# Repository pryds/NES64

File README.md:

# Moved

The NES64 project has moved to [GitLab](https://gitlab.com/nes64/NES64)

NES64 homepage: [nes64.autumnhippo.com](http://nes64.autumnhippo.com)

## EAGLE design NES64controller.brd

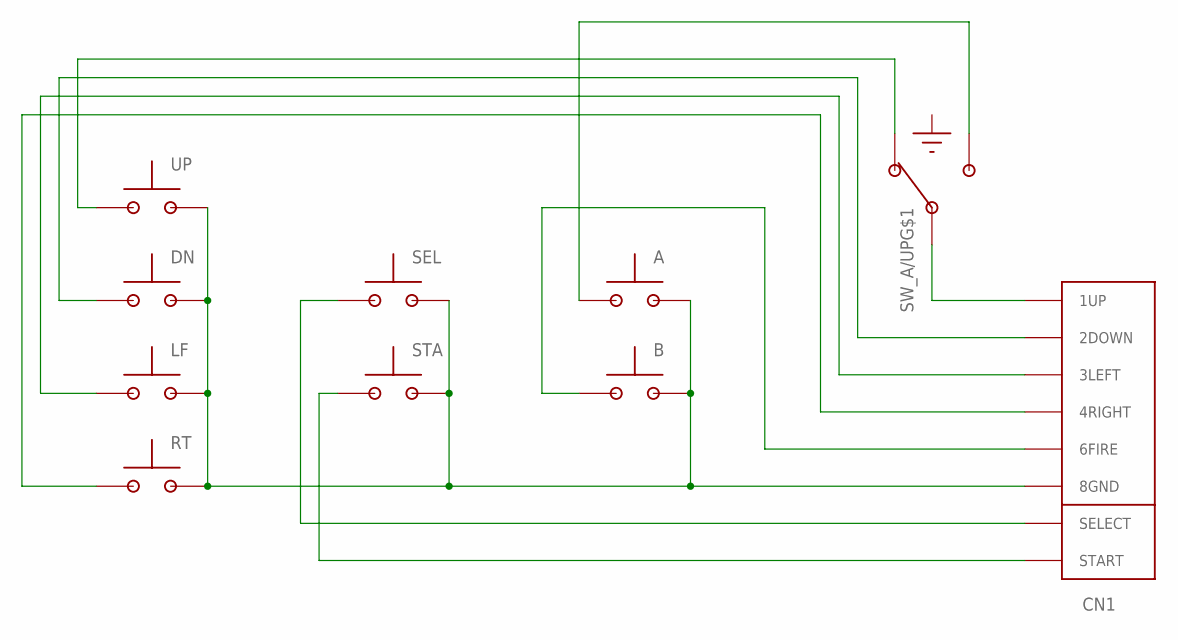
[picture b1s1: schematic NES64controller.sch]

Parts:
A: RUBBERBUTTON_CONTACTAREA_9MM
B: RUBBERBUTTON_CONTACTAREA_9MM
CN1: NES64_CONNECTOR
DN: RUBBERBUTTON_CONTACTAREA_9MM
LF: RUBBERBUTTON_CONTACTAREA_9MM
RT: RUBBERBUTTON_CONTACTAREA_9MM
SEL: RUBBERBUTTON_CONTACTAREA_9MM
STA: RUBBERBUTTON_CONTACTAREA_9MM
SW_A/UP: TOGGLESWITCH_SPDT_SMALL_90DEG
UP: RUBBERBUTTON_CONTACTAREA_9MM

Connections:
unnamed: A.B, B.B, CN1.8GND, DN.B, LF.B, RT.B, SEL.B, STA.B, UP.B
unnamed: CN1.1UP, SW_A/UP.N
unnamed: B.A, CN1.6FIRE
unnamed: CN1.START, STA.A
unnamed: CN1.SELECT, SEL.A
unnamed: CN1.4RIGHT, RT.A
unnamed: CN1.3LEFT, LF.A
unnamed: CN1.2DOWN, DN.A
unnamed: SW_A/UP.A, UP.A
unnamed: A.A, SW_A/UP.B

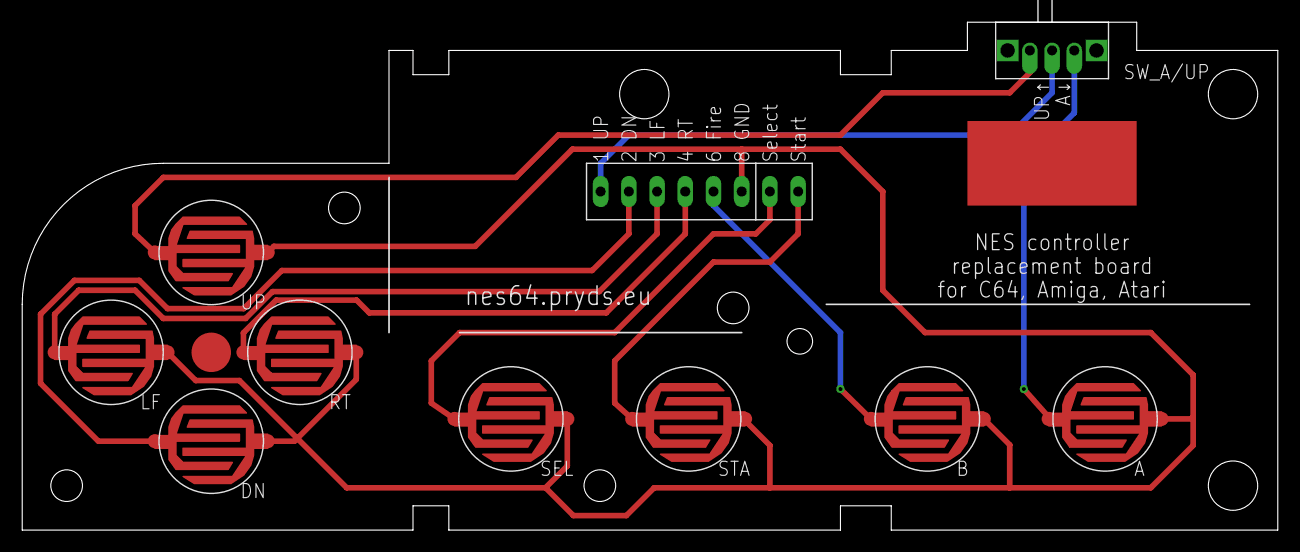
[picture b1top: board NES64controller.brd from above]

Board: 2 copper layers, 113.0 x 45.7 mm, 10 parts (0 on the bottom side), 10 nets.

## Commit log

2020-03-07 First version
2020-04-11 Adjustment of hole size in lower right corner and edge notches to fit USB controller case; slight correcting translation of top holes and middle small hole downwards; removing small area of solder ma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
2020-04-11 Added labelling of switch and connector
2020-04-23 Minor silkscreen changes
2020-04-23 Re-write of Readme file
2020-04-23 Minor Readme file corrections
2020-04-23 Gerber file for v0.2
2020-04-27 Moved to GitLab
2021-08-05 New address
